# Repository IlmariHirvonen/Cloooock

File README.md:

# Cloooock
A simple Arduino based eurorack clock module. I may add some stuff in the future like encoder acceleration.

Current functionality:
* BPM adjustment 30-9999 bpm
* Pause and play
* Time division adjustment
  * Press encoder to enter channel selection
  * Press encoder to select channel
  * Select with encoder between 1/1 to 1/128
  * Press encoder to go back to channel selection or play/pause button to restart clock

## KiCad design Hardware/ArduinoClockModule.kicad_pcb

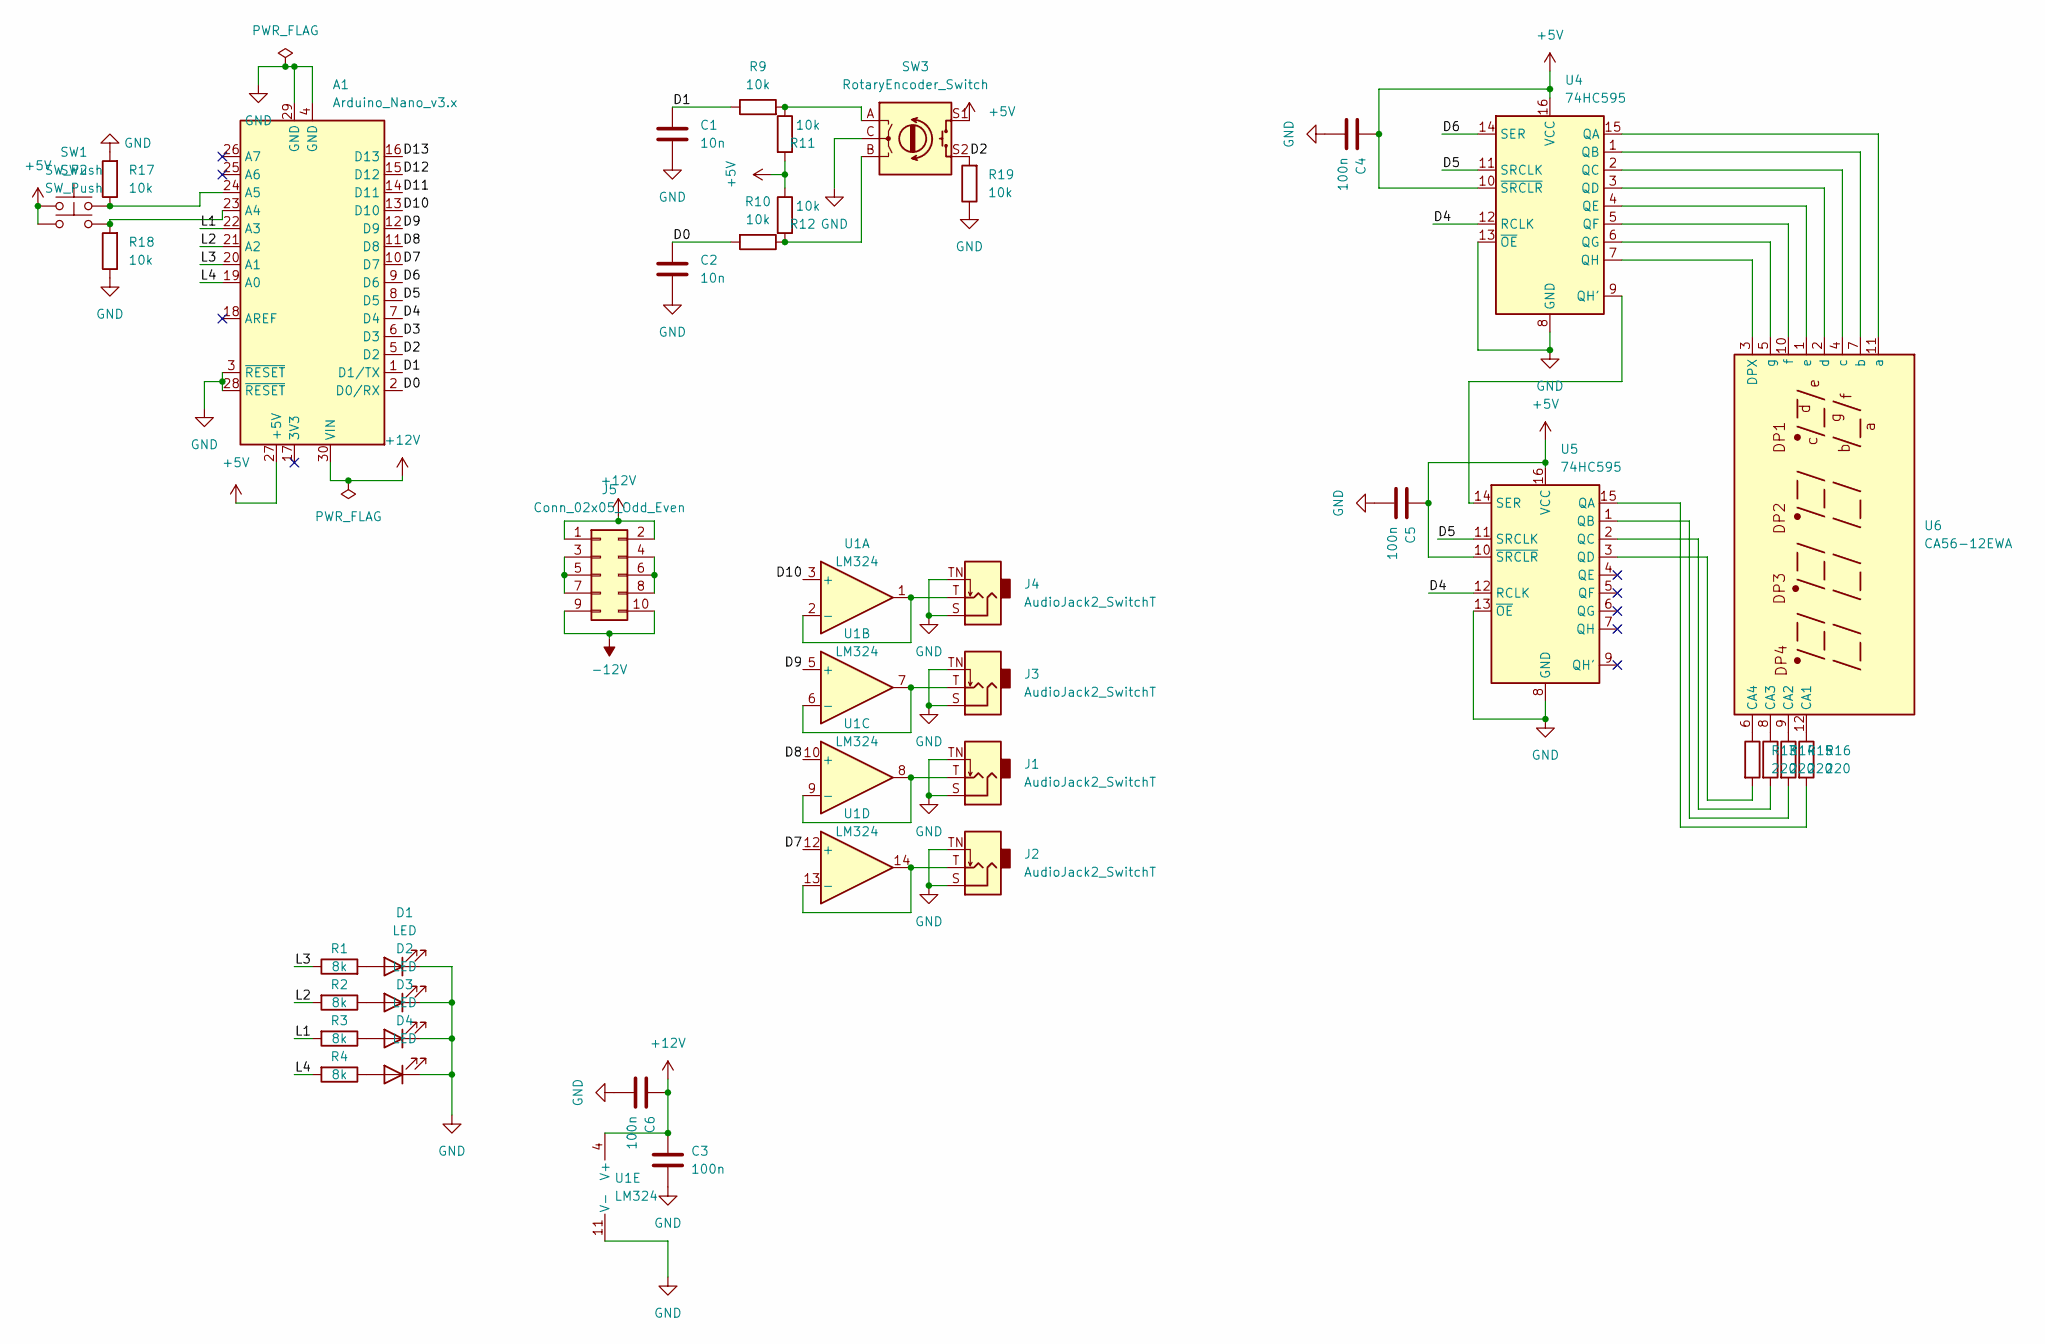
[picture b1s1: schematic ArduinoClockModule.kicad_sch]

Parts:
A1: Arduino_Nano_v3.x; Arduino_Nano
C1, C2: 10n; C_Disc_D3.0mm_W2.0mm_P2.50mm
C3, C4, C5, C6: 100n; C_Disc_D3.8mm_W2.6mm_P2.50mm
D1, D2, D3, D4: LED; LED_D3.0mm
J1, J2, J3, J4: AudioJack2_SwitchT; Thonkiconn
J5: Conn_02x05_Odd_Even; PinHeader_2x05_P2.54mm_Vertical
R1, R2, R3, R4: 8k; R_Axial_DIN0207_L6.3mm_D2.5mm_P7.62mm_Horizontal
R9, R10, R11, R12, R17, R18, R19: 10k; R_Axial_DIN0207_L6.3mm_D2.5mm_P7.62mm_Horizontal
R13, R14, R15, R16: 220; R_Axial_DIN0207_L6.3mm_D2.5mm_P7.62mm_Horizontal
SW1, SW2: SW_Push; SW_PUSH_6mm
SW3: RotaryEncoder_Switch; RotaryEncoder_Alps_EC11E-Switch_Vertical_H20mm
U1: LM324; DIP-14_W7.62mm
U4, U5: 74HC595; DIP-16_W7.62mm
U6: CA56-12EWA

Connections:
+5V: A1.27 (+5V), C4.1, C5.1, R11.2, R12.1, SW1.1, SW2.1, SW3.S1, U4.10 (~SRCLR), U4.16 (VCC), U5.10 (~SRCLR), U5.16 (VCC)
+12V: A1.30 (VIN), C3.1, C6.1, J5.1, J5.2, U1.4 (V+)
-12V: J5.9, J5.10
/D0: A1.2 (D0/RX), C2.1, R10.2
/D1: A1.1 (D1/TX), C1.1, R9.1
/D2: A1.5 (D2), R19.2, SW3.S2
/D3: A1.6 (D3)
/D4: A1.7 (D4), U4.12 (RCLK), U5.12 (RCLK)
/D5: A1.8 (D5), U4.11 (SRCLK), U5.11 (SRCLK)
/D6: A1.9 (D6), U4.14 (SER)
/D7: A1.10 (D7), U1.12 (+)
/D8: A1.11 (D8), U1.10 (+)
/D9: A1.12 (D9), U1.5 (+)
/D10: A1.13 (D10), U1.3 (+)
/D11: A1.14 (D11)
/D12: A1.15 (D12)
/D13: A1.16 (D13)
/L1: A1.22 (A3), R3.2
/L2: A1.21 (A2), R2.2
/L3: A1.20 (A1), R1.1
/L4: A1.19 (A0), R4.2
GND: A1.3 (~RESET), A1.4 (GND), A1.28 (~RESET), A1.29 (GND), C1.2, C2.2, C3.2, C4.2, C5.2, C6.2, D1.1 (K), D2.1 (K), D3.1 (K), D4.1 (K), J1.S, J1.TN, J2.S, J2.TN, J3.S, J3.TN, J4.S, J4.TN, R17.2, R18.1, R19.1, SW3.C, U1.11 (V-), U4.8 (GND), U4.13 (~OE), U5.8 (GND), U5.13 (~OE)
unnamed: A1.23 (A4), R18.2, SW2.2
unnamed: A1.24 (A5), R17.1, SW1.2
unnamed: D1.2 (A), R1.2
unnamed: D2.2 (A), R2.1
unnamed: D3.2 (A), R3.1
unnamed: D4.2 (A), R4.1
unnamed: J1.T, U1.8, U1.9 (-)
unnamed: J2.T, U1.13 (-), U1.14
unnamed: J3.T, U1.6 (-), U1.7
unnamed: J4.T, U1.1, U1.2 (-)
unnamed: J5.3, J5.5, J5.7
unnamed: J5.4, J5.6, J5.8
unnamed: R10.1, R12.2, SW3.B
unnamed: R9.2, R11.1, SW3.A
unnamed: R13.1, U6.6 (CA4)
unnamed: R13.2, U5.3 (QD)
unnamed: R14.1, U6.8 (CA3)
unnamed: R14.2, U5.2 (QC)
unnamed: R15.1, U6.9 (CA2)
unnamed: R15.2, U5.1 (QB)
unnamed: R16.1, U6.12 (CA1)
unnamed: R16.2, U5.15 (QA)
unnamed: U4.1 (QB), U6.7 (b)
unnamed: U4.2 (QC), U6.4 (c)
unnamed: U4.3 (QD), U6.2 (d)
unnamed: U4.4 (QE), U6.1 (e)
unnamed: U4.5 (QF), U6.10 (f)
unnamed: U4.6 (QG), U6.5 (g)
unnamed: U4.7 (QH), U6.3 (DPX)
unnamed: U4.15 (QA), U6.11 (a)
unnamed: U4.9 (QH'), U5.14 (SER)

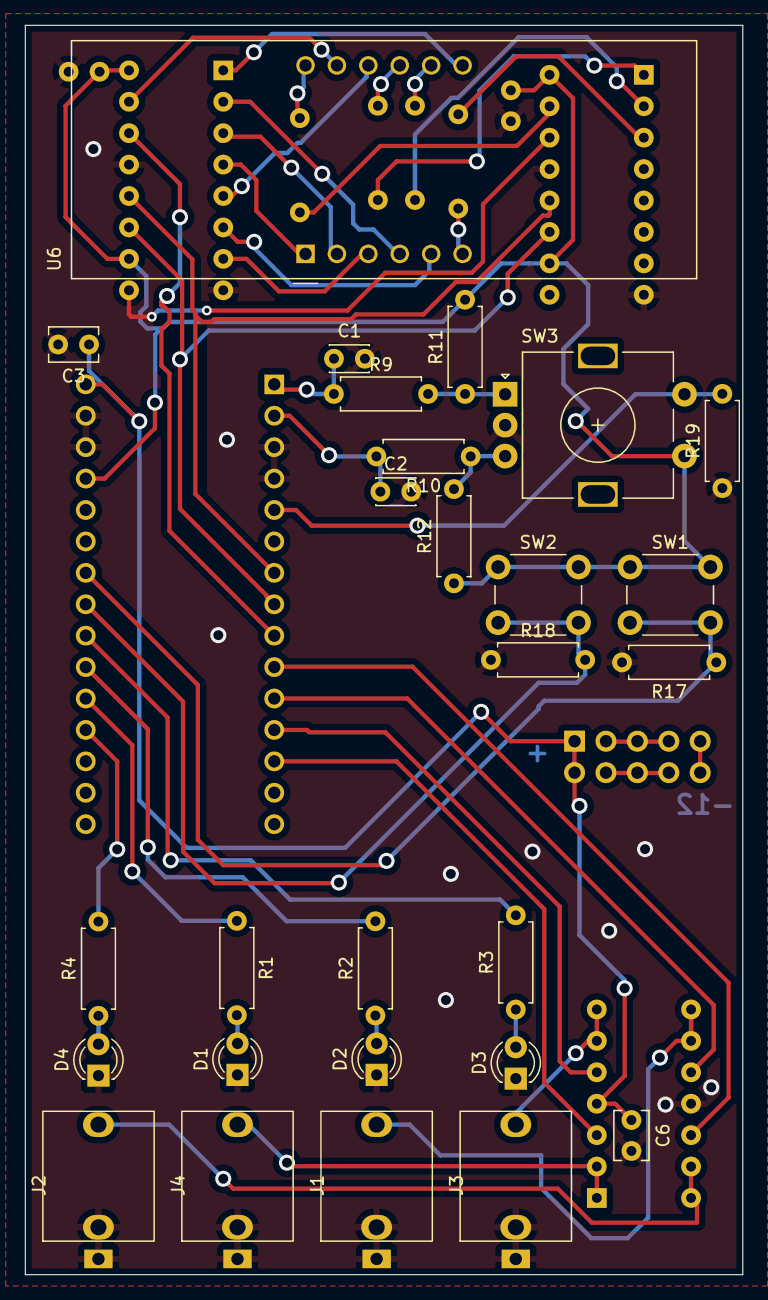
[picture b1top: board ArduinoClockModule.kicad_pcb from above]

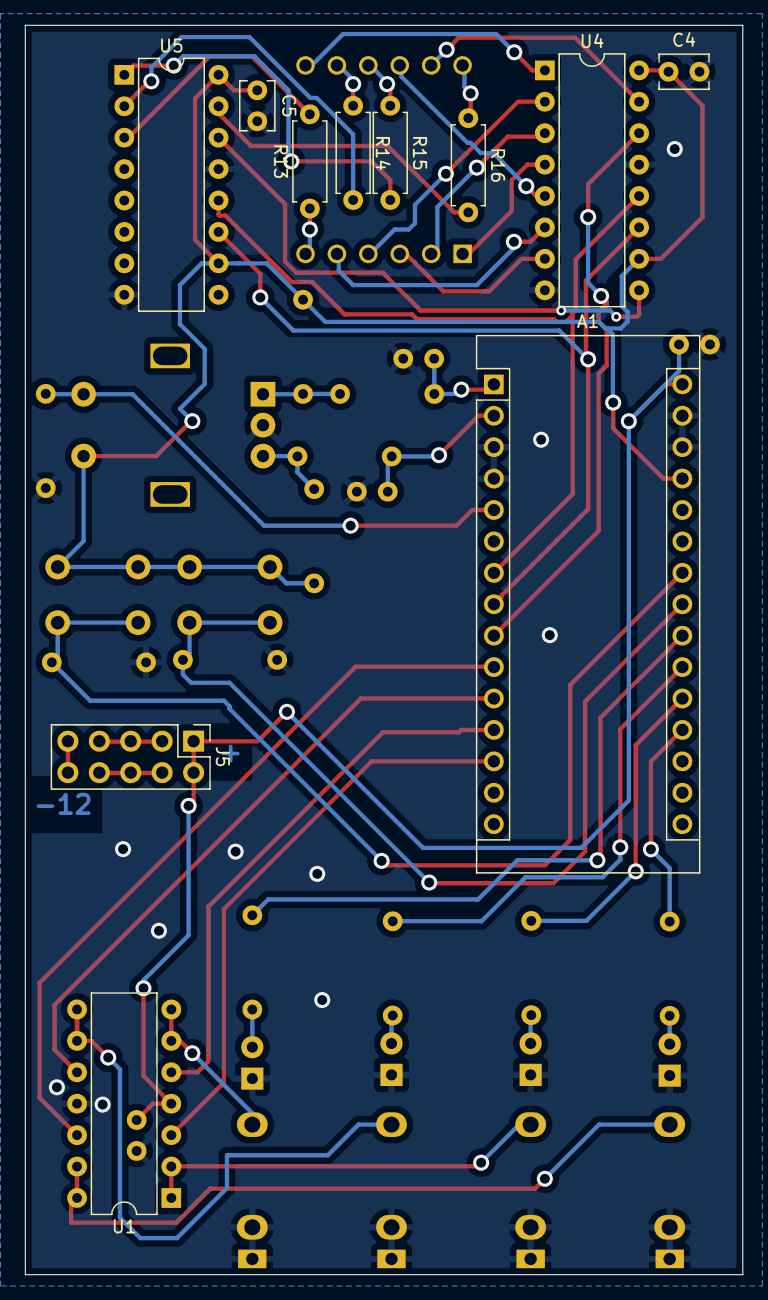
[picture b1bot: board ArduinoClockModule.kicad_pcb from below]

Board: 2 copper layers, 58.0 x 101.0 mm, 38 parts (11 on the bottom side), 49 nets.

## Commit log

2022-12-15 added licenses
2022-12-23 First working protorype. The class should allow some expansion of features wihtout too major refactors. Some modifications to the hardware is still needed.
2022-12-25 Rewriting in rust. Work in progress
2022-12-27 wip: add clock channels
2022-12-27 fix bpm wrapping
2022-12-28 Punkit pois! (static mut -> RefCell)
2022-12-28 save bug
2022-12-29 now gives consistent clock output with even prescaler denominators
2022-12-29 added a basic pause functionaluty
2023-01-24 Update README.md
    added some progress notes
2023-07-24 Added ways to change numerator of each clock channel
2023-07-24 Some basic cleanup
